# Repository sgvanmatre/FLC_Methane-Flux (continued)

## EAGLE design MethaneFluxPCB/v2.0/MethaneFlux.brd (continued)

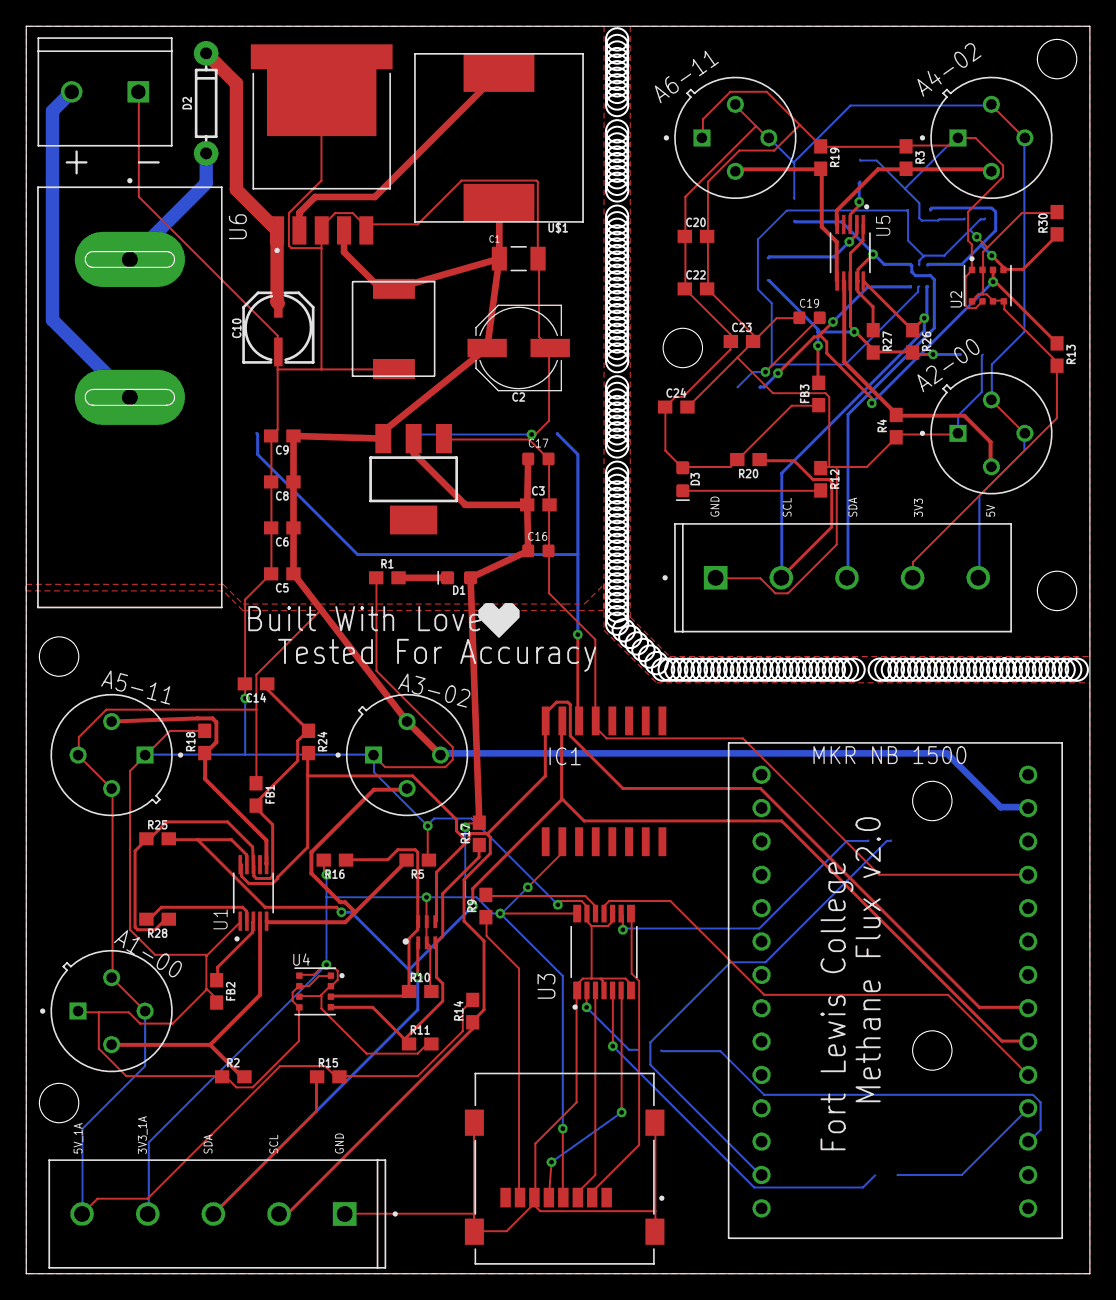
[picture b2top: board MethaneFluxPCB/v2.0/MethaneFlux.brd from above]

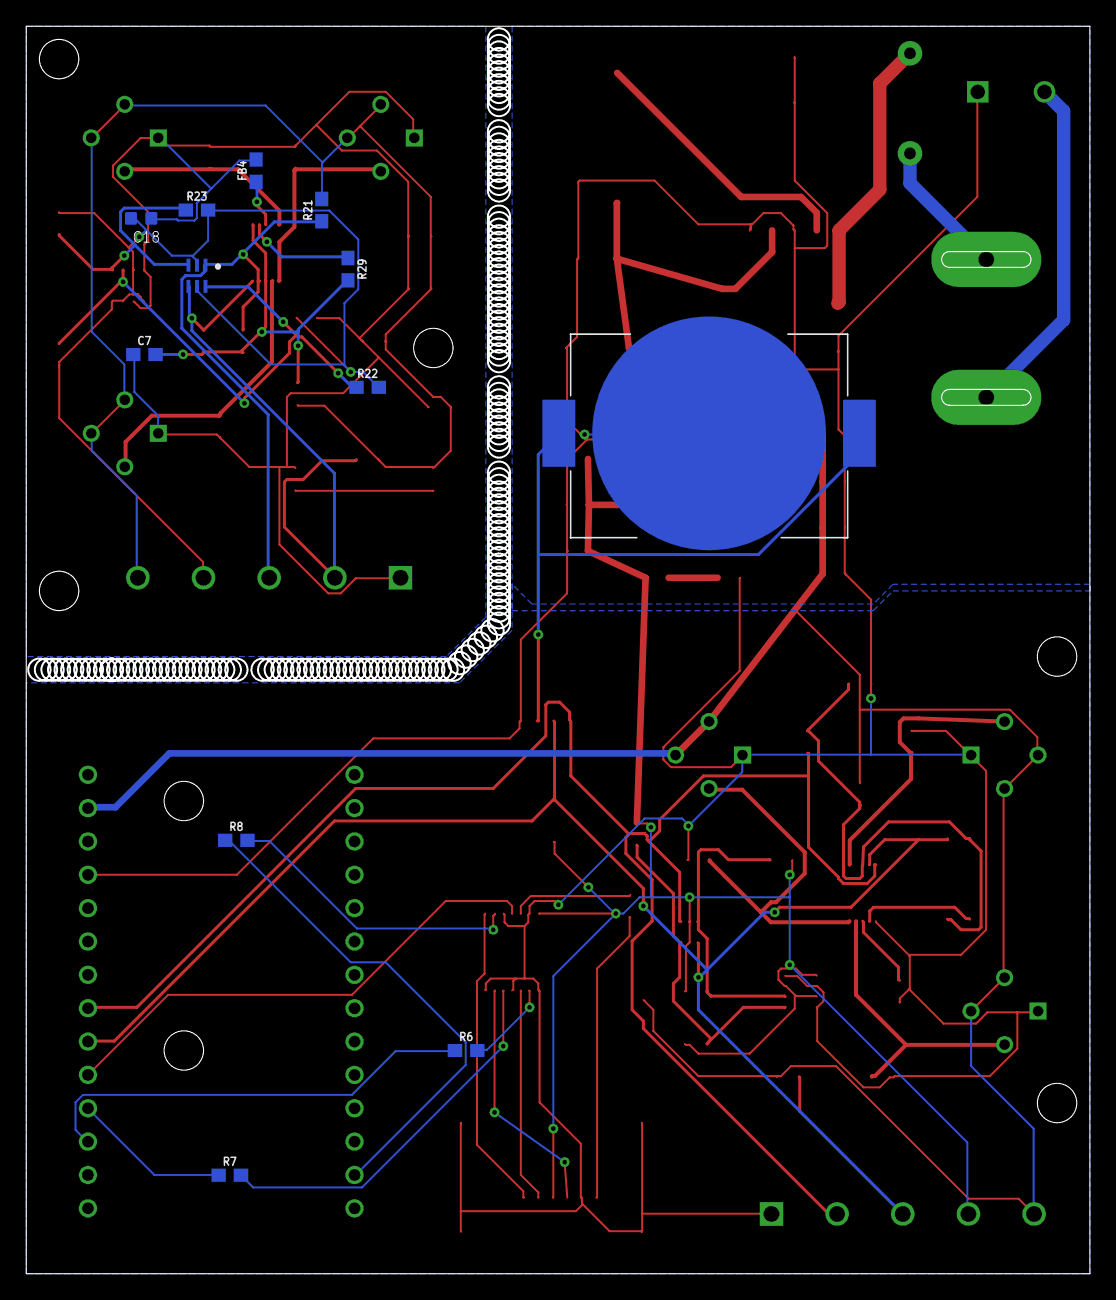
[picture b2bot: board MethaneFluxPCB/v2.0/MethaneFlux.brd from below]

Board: 2 copper layers, 80.8 x 94.8 mm, 82 parts (12 on the bottom side), 45 nets.

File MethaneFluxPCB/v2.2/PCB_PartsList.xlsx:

Qty | Value | Package | Parts | URL
2 | 1.0uF | 603 | C7, C14 | https://www.digikey.com/product-detail/en/samsung-electro-me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
14 | 10k | 603 | R14, R15, R16, R17, R20, R21, R22, R23, R24, R25, R26, R27, R28, R29 | https://www.digikey.com/en/products/detail/stackpole-electro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
8 | 10uF | 603 | C5, C6, C8, C9, C20, C22, C23, C24 | https://www.digikey.com/en/products/detail/samsung-electro-m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
2 | 282836-5 | TE_282836-5 | J1, J2 | https://www.digikey.com/en/products/detail/te-connectivity-a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
1 | 282837-2 | TE_282837-2 | P1 | https://www.digikey.com/en/products/detail/te-connectivity-a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
2 | 2N7002DW | SOT363 | U$3, U$4 | https://www.digikey.com/en/products/detail/onsemi/2N7002DW/1785764
4 | 3.3k | 603 | R6, R7, R8, R9 | https://www.digikey.com/en/products/detail/koa-speer-electro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
4 | 30Ω/1.8A | 603 | FB1, FB2, FB3, FB4 | https://www.digikey.com/en/products/detail/murata-electronic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
4 | 4.7k | 603 | R10, R11, R13, R30 | https://www.digikey.com/en/products/detail/yageo/RC0402JR-07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
8 | 470 | 603 | R1, R2, R3, R4, R5, R12, R18, R19 | https://www.digikey.com/product-detail/en/RC0603JR-07470RL/3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
1 | 74LVC125APW,118 | IC_74LVC125APW,118 | U3 | https://www.digikey.com/en/products/detail/nexperia-usa-inc/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
2 | ADS1115IDGSR | SOP50P490X110-10N | U1, U5 | https://www.digikey.com/en/products/detail/texas-instruments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
1 | BAT-HLD-001 | BAT_BAT-HLD-001 | BT1 | https://www.digikey.com/en/products/detail/te-connectivity-l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
2 | BME680 | PSON80P300X300X100-8N | U2, U4 | https://www.digikey.com/en/products/detail/bosch-sensortec/B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
1 | DS3231/SO | SO16W | IC1 | https://www.digikey.com/en/products/detail/analog-devices-in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
1 | GTFH08131YHR | AMPHENOL_GTFH08131YHR | J3 | https://www.digikey.com/en/products/detail/amphenol-cs-comme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
1 | IN_47UH_3.8A_SMD | INDUCTOR_4X4MM | US1 | https://www.digikey.com/en/products/detail/w-rth-elektronik/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
1 | IN_33UH_3.8A_SMD | INDUCTOR_4X4MM | U$7 | https://www.digikey.com/en/products/detail/w%C3%BCrth-elektr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
1 | LM2596S-5 | VREG_LM2596S-5 | U6 | https://www.digikey.com/en/products/detail/texas-instruments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
2 | LM2596S-3.3 | VREG_LM2596S-3.3 | U7 | https://www.digikey.com/en/products/detail/texas-instruments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
1 | MKRNB1500 | MRKNB1500 | U$5 | https://www.digikey.com/en/products/detail/arduino/ABX00019/9486709
1 | RB141C1100 | SW_RB141C1100 | S1 | https://www.digikey.com/en/products/detail/e-switch/RB141C11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
2 | Yellow | LED-0603 | D1, D3 | https://www.digikey.com/en/products/detail/w%C3%BCrth-elektr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
2 | SS34_214AB | SOD-323 | U$2, U$6 | https://www.digikey.com/product-detail/en/on-semiconductor/S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
2 | TAJC227K006RNJ | CAPPM6032X280N | C1, C2 | https://www.digikey.com/en/products/detail/kyocera-avx/TAJC2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
2 | TAJD107K016RNJ | CAPPM7344X310N | C3, C4 | https://www.digikey.com/en/products/detail/kyocera-avx/TAJD1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
2 | TGS2600 | TO255P920H830-4 | A1-00, A2-00
2 | TGS2602 | TGS2602 | A3-02, A4-02
2 | TGS2611 | TGS2611 | A5-11, A6-11
4 | VJ0603Y104KLXAC5G | CAPC1608X92N | C16, C17, C18, C19 | https://www.digikey.com/en/products/detail/nextgen-component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

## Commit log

2024-05-02 Rename MethaneFluxPCB/PCB_PartsList.xlsx to MethaneFluxPCB/v2.2/PCB_PartsList.xlsx
2024-07-10 Add files via upload
    Calibration Test File
